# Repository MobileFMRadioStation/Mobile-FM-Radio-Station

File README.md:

#Mobile-FM-Radio-Station
 Mobile FM Radio for Communicating Resilience<BR>

#Product
 Mobile FM Radio Station Kit is consists of;<BR>
  1. easy controllable application for making, recording and broadcasting radio contents<BR>
  2. Inexpensive 3-10 watt FM transmitter for radio wave transmission<BR>
  3. Transmitter antenna<BR>

#Latest Application Download
  https://github.com/MobileFMRadioStation/Mobile-FM-Radio-Station/releases<BR>
 
#Source
 MobileRadioStation folder contains source code for application.<BR>
 Trasnmitter folder contains the specification for hardware.<BR>

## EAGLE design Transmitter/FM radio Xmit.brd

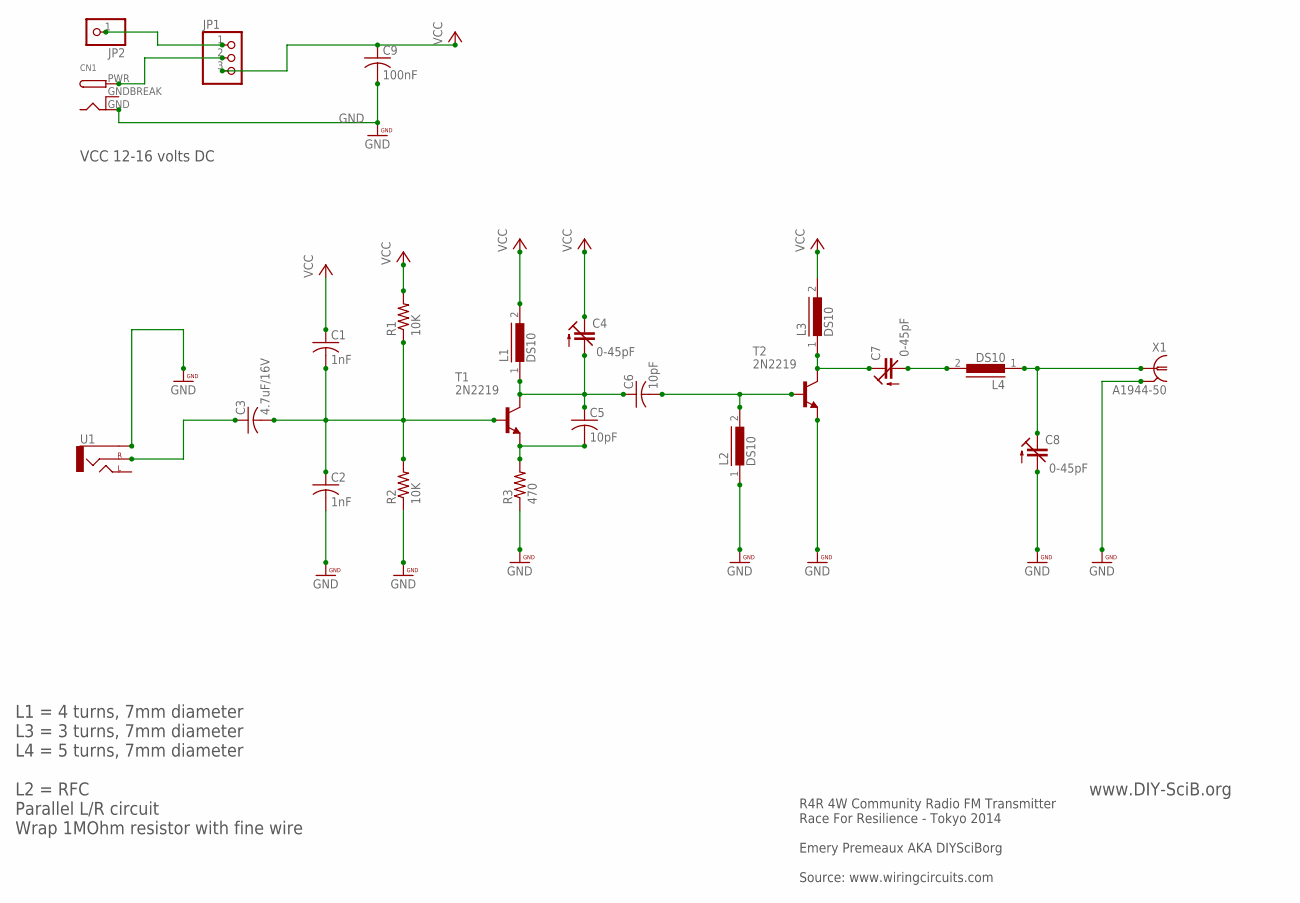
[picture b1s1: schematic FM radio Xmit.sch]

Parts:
C1, C2: 1nF; C025-024X044
C3: 4.7uF/16V; C025-024X044
C4, C7, C8: 0-45pF; 3008
C5, C6: 10pF; C025-024X044
C9: 100nF; C025-024X044
CN1: DCBARRELPTH; DCJACK_2MM_PTH
JP1: PINHD-1X3; 1X03
JP2: PINHD-1X1; 1X01
L1, L2, L3, L4: DS10
R1, R2: 10K; 0204/7
R3: 470; 0204/7
T1, T2: 2N2219; TO5
U1: AUDIO-JACK2.5MM; STEREOJACK2.5MM_STEREOJACK2.5MM
X1: A1944-50; A1944

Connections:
GND: C2.2, C8.- (A), C9.2, CN1.GND, L2.1, R2.1, R3.1, T2.1 (E), U1.RING1 (SLEEVE), X1.2, X1.3 (2), X1.4 (2), X1.5 (2)
GNDBREAK: CN1.GNDBREAK
unnamed: C1.2, C2.1, C3.2, R1.1, R2.2, T1.2 (B)
unnamed: C7.+ (E), L3.1, T2.3 (C)
unnamed: C3.1, U1.TIP (RIGHT)
unnamed: C5.2, R3.2, T1.1 (E)
unnamed: C6.2, L2.2, T2.2 (B)
unnamed: C4.- (A), C5.1, C6.1, L1.1, T1.3 (C)
unnamed: C7.- (A), L4.2
unnamed: C8.+ (E), L4.1, X1.1
unnamed: JP1.1, JP2.1
PWR: CN1.PWR, JP1.2
VCC: C1.1, C4.+ (E), C9.1, JP1.3, L1.2, R1.2
X: L3.2

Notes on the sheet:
R4R 4W Community Radio FM Transmitter Race For Resilience - Tokyo 2014 Emery Premeaux AKA DIYSciBorg Source: www.wiringcircuits.com
L1 = 4 turns, 7mm diameter L3 = 3 turns, 7mm diameter L4 = 5 turns, 7mm diameter L2 = RFC Parallel L/R circuit Wrap 1MOhm resistor with fine wire
VCC 12-16 volts DC
www.DIY-SciB.org

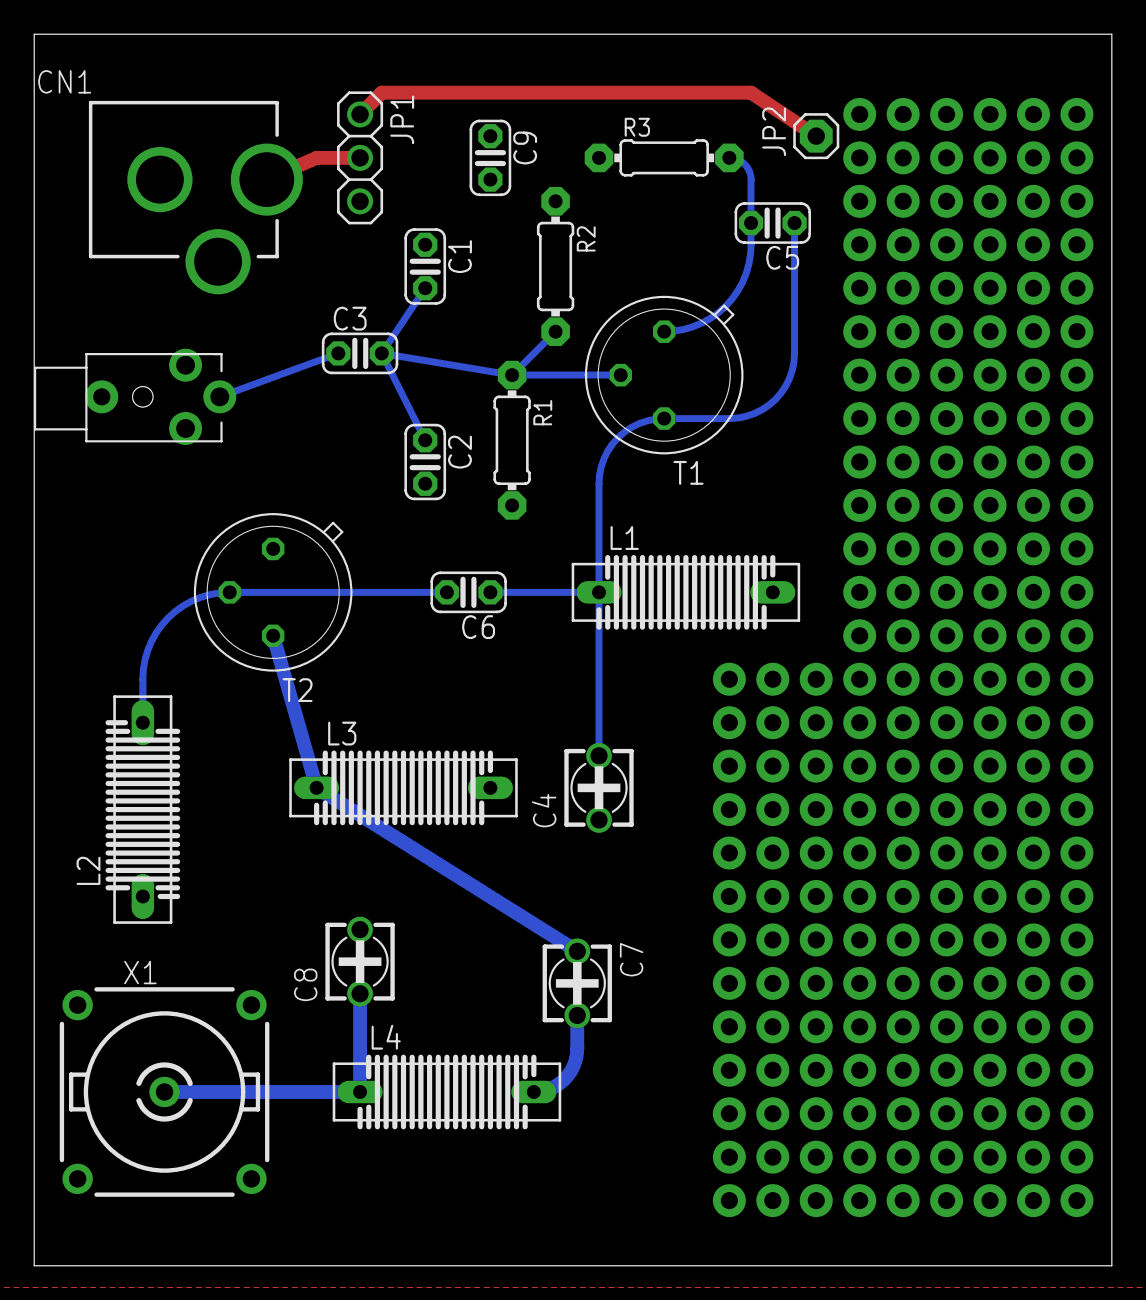
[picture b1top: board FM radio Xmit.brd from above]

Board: 2 copper layers, 63.0 x 72.0 mm, 23 parts (0 on the bottom side), 12 nets.

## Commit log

2014-02-15 V1.0 BETA
    Primary radio xmitter hardware test board
2014-05-10 mv files
2014-05-10 mv files again

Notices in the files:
parts and their libraries:
SparkFun-Connectors: Licensing: CC v3.0 Share-Alike You are welcome to use this library for commercial purposes.
PatternAgents-Beautify: License : http://creativecommons.org/licenses/by-sa/3.0
(Creative Commons 3.0)
